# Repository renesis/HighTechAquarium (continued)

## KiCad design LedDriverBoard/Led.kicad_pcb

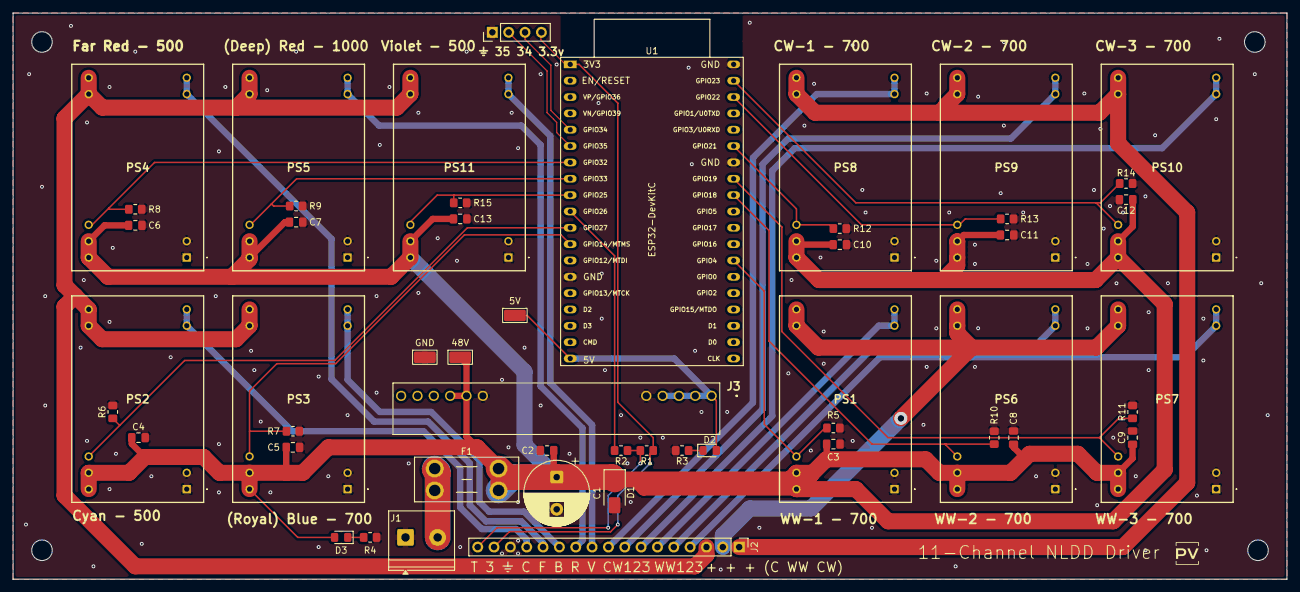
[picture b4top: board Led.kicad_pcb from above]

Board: 2 copper layers, 198.0 x 88.0 mm, 50 parts (0 on the bottom side), 34 nets.

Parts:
5V, 48V: TestPoint_Keystone_5015_Micro_Mini
C1: 220uF 63V; CP_Radial_D10.0mm_P5.00mm
C2: 0.1uF; C_0805_2012Metric_Pad1.18x1.45mm_HandSolder
C3, C4, C5, C6, C7, C8, C9, C10, C11, C12, C13: 2.2uF; C_0805_2012Metric_Pad1.18x1.45mm_HandSolder
D1: SMAJ48A; D_SMA
D2, D3: LED; LED_0805_2012Metric_Pad1.15x1.40mm_HandSolder
F1: 5A; Fuseholder_Blade_Mini_Keystone_3568
GND: TestPoint_Keystone_5015_Micro_Mini
J1: 48V IN; TerminalBlock_Phoenix_PT-1,5-2-5.0-H_1x02_P5.00mm_Horizontal
J2: Conn_01x17; PinHeader_1x17_P2.54mm_Vertical
J3: NID35-5; NID355
PS1, PS2, PS3, PS4, PS5, PS6, PS7, PS8, PS9, PS10, PS11: NLDD-700H; NLDD700H
R1: 4.7k; R_0805_2012Metric_Pad1.20x1.40mm_HandSolder
R2: 100R; R_0805_2012Metric_Pad1.20x1.40mm_HandSolder
R3: 1k; R_0805_2012Metric_Pad1.20x1.40mm_HandSolder
R4: 22k; R_0805_2012Metric_Pad1.20x1.40mm_HandSolder
R5, R6, R7, R8, R9, R10, R11, R12, R13, R14, R15: 10k; R_0805_2012Metric_Pad1.20x1.40mm_HandSolder
U1: ESP32-DevKitC

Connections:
+3V3: J2.16, R1.1, U1.1 (3V3)
+5V: 5V.1, D2.2 (A), J3.1 (+VOUT_1), J3.2 (+VOUT_2), J3.3 (+VOUT_3), J3.4 (+VOUT_4), U1.19 (5V)
+48V: 48V.1, C1.1, C2.1, C3.1, C4.1, C5.1, C6.1, C7.1, C8.1, C9.1, C10.1, C11.1, C12.1, C13.1, D1.1 (A1), D3.2 (A), F1.2, J3.7 (+VIN_1), J3.8 (+VIN_2), PS1.23 (+VIN_1), PS1.24 (+VIN_2), PS2.23 (+VIN_1), PS2.24 (+VIN_2), PS3.23 (+VIN_1), PS3.24 (+VIN_2), PS4.23 (+VIN_1), PS4.24 (+VIN_2), PS5.23 (+VIN_1), PS5.24 (+VIN_2), PS6.23 (+VIN_1), PS6.24 (+VIN_2), PS7.23 (+VIN_1), PS7.24 (+VIN_2), PS8.23 (+VIN_1), PS8.24 (+VIN_2), PS9.23 (+VIN_1), PS9.24 (+VIN_2), PS10.23 (+VIN_1), PS10.24 (+VIN_2), PS11.23 (+VIN_1), PS11.24 (+VIN_2)
GND: C1.2, C2.2, C3.2, C4.2, C5.2, C6.2, C7.2, C8.2, C9.2, C10.2, C11.2, C12.2, C13.2, D1.2 (A2), GND.1, J1.1, J2.15, J3.5 (COM_1), J3.6 (COM_2), PS1.1 (-VIN_1), PS1.2 (-VIN_2), PS2.1 (-VIN_1), PS2.2 (-VIN_2), PS3.1 (-VIN_1), PS3.2 (-VIN_2), PS4.1 (-VIN_1), PS4.2 (-VIN_2), PS5.1 (-VIN_1), PS5.2 (-VIN_2), PS6.1 (-VIN_1), PS6.2 (-VIN_2), PS7.1 (-VIN_1), PS7.2 (-VIN_2), PS8.1 (-VIN_1), PS8.2 (-VIN_2), PS9.1 (-VIN_1), PS9.2 (-VIN_2), PS10.1 (-VIN_1), PS10.2 (-VIN_2), PS11.1 (-VIN_1), PS11.2 (-VIN_2), R3.2, R4.2, R5.2, R6.2, R7.2, R8.2, R9.2, R10.2, R11.2, R12.2, R13.2, R14.2, R15.2, U1.14 (GND), U1.32 (GND), U1.38 (GND)
LEDCOLOR+: J2.3, PS2.13 (+VOUT_1), PS2.14 (+VOUT_2), PS3.13 (+VOUT_1), PS3.14 (+VOUT_2), PS4.13 (+VOUT_1), PS4.14 (+VOUT_2), PS5.13 (+VOUT_1), PS5.14 (+VOUT_2), PS11.13 (+VOUT_1), PS11.14 (+VOUT_2)
LEDCW+: J2.1, PS8.13 (+VOUT_1), PS8.14 (+VOUT_2), PS9.13 (+VOUT_1), PS9.14 (+VOUT_2), PS10.13 (+VOUT_1), PS10.14 (+VOUT_2)
LEDWW+: J2.2, PS1.13 (+VOUT_1), PS1.14 (+VOUT_2), PS6.13 (+VOUT_1), PS6.14 (+VOUT_2), PS7.13 (+VOUT_1), PS7.14 (+VOUT_2)
LED_CH1-: J2.6, PS1.11 (-VOUT_1), PS1.12 (-VOUT_2)
LED_CH2-: J2.14, PS2.11 (-VOUT_1), PS2.12 (-VOUT_2)
LED_CH3-: J2.12, PS3.11 (-VOUT_1), PS3.12 (-VOUT_2)
LED_CH4-: J2.13, PS4.11 (-VOUT_1), PS4.12 (-VOUT_2)
LED_CH5-: J2.11, PS5.11 (-VOUT_1), PS5.12 (-VOUT_2)
LED_CH6-: J2.5, PS6.11 (-VOUT_1), PS6.12 (-VOUT_2)
LED_CH7-: J2.4, PS7.11 (-VOUT_1), PS7.12 (-VOUT_2)
LED_CH8-: J2.9, PS8.11 (-VOUT_1), PS8.12 (-VOUT_2)
LED_CH9-: J2.8, PS9.11 (-VOUT_1), PS9.12 (-VOUT_2)
LED_CH10-: J2.7, PS10.11 (-VOUT_1), PS10.12 (-VOUT_2)
LED_CH11-: J2.10, PS11.11 (-VOUT_1), PS11.12 (-VOUT_2)
unnamed: D2.1 (K), R3.1
unnamed: D3.1 (K), R4.1
unnamed: F1.1, J1.2
unnamed: R2.2, U1.10 (DAC_2/ADC2_CH9/GPIO26)
PWM_CH1: PS1.22 (PWM_DIM), R5.1, U1.26 (ADC2_CH0/GPIO4)
PWM_CH2: PS2.22 (PWM_DIM), R6.1, U1.11 (ADC2_CH7/GPIO27)
PWM_CH3: PS3.22 (PWM_DIM), R7.1, U1.12 (MTMS/GPIO14/ADC2_CH6)
PWM_CH4: PS4.22 (PWM_DIM), R8.1, U1.7 (32K_XP/GPIO32/ADC1_CH4)
PWM_CH5: PS5.22 (PWM_DIM), R9.1, U1.8 (32K_XN/GPIO33/ADC1_CH5)
PWM_CH6: PS6.22 (PWM_DIM), R10.1, U1.30 (GPIO18)
PWM_CH7: PS7.22 (PWM_DIM), R11.1, U1.31 (GPIO19)
PWM_CH8: PS8.22 (PWM_DIM), R12.1, U1.33 (GPIO21)
PWM_CH9: PS9.22 (PWM_DIM), R13.1, U1.36 (GPIO22)
PWM_CH10: PS10.22 (PWM_DIM), R14.1, U1.37 (GPIO23)
PWM_CH11: PS11.22 (PWM_DIM), R15.1, U1.9 (DAC_1/ADC2_CH8/GPIO25)
TEMP_DATA: J2.17, R1.2, R2.1

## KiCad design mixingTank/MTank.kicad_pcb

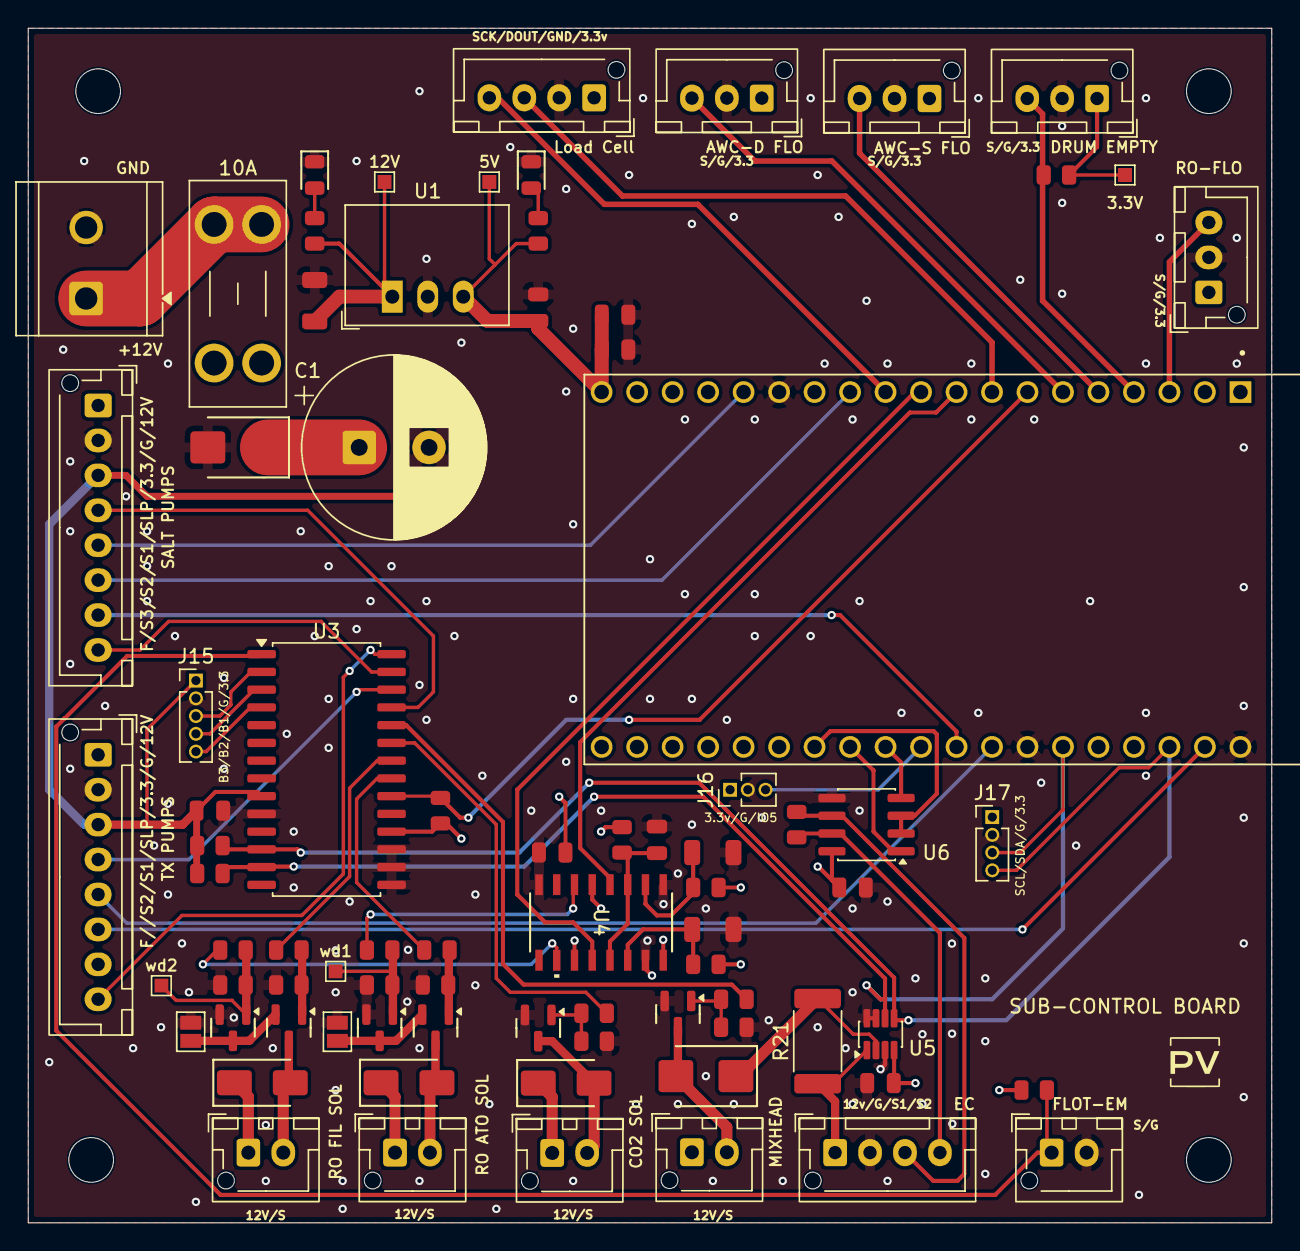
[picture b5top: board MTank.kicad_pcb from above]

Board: 4 copper layers, 89.0 x 85.5 mm, 80 parts (0 on the bottom side), 59 nets.

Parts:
3.3V, 5V, 12V: TestPoint; TestPoint_Pad_1.0x1.0mm
10A: 10A; Fuseholder_Blade_Mini_Keystone_3568
AWC-D FLO: AWC-FLO D; JST_XH_B3B-XH-AM_1x03_P2.50mm_Vertical
AWC-S FLO: AWC-FLO; JST_XH_B3B-XH-AM_1x03_P2.50mm_Vertical
C1: 1000uF; CP_Radial_D13.0mm_P5.00mm
C2: 22uF; C_0805
C3: 10uF; C_0805
C4, C7, C8: 10uF; C_1206
C5, C6, C10, C11, C12: 100nF; C_0805
C9: 1uF; C_0805
CO2 SOL: CO2 SOL; JST_XH_B2B-XH-AM_1x02_P2.50mm_Vertical
D1: SMBJ16A; D_SMB
D2, D3: Green; D_0805
D4, D5, D6: SS14; D_SMA
D8: SS24; D_SMB
DRUM EMPTY: DRUM; JST_XH_B3B-XH-AM_1x03_P2.50mm_Vertical
EC: EC Probe; JST_XH_B4B-XH-AM_1x04_P2.50mm_Vertical
FLOT-EM: EM; JST_XH_B2B-XH-AM_1x02_P2.50mm_Vertical
J1: 12V IN; TerminalBlock_CUI_TB007-508-02_1x02_P5.08mm_Horizontal
J15: Conn_01x05; PinHeader_1x05_P1.27mm_Vertical
J16: Screw_Terminal_01x03; PinHeader_1x03_P1.27mm_Vertical
J17: Conn_01x04; PinHeader_1x04_P1.27mm_Vertical
JP1, JP2: WD Bypass; SolderJumper-2_P1.3mm_Open_Pad1.0x1.5mm
Load Cell: LoadCell; JST_XH_B4B-XH-AM_1x04_P2.50mm_Vertical
MIXHEAD: CO2 SOL; JST_XH_B2B-XH-AM_1x02_P2.50mm_Vertical
Q1, Q2, Q3, Q4, Q5, Q6: AO3400A; Q_SOT-23
R1: 2.2kΩ; R_0805
R2: 1kΩ; R_0805
R3, R4: 4.7kΩ; R_0805
R5, R7, R10, R13, R14, R16, R18, R20, R23, R24: 10kΩ; R_0805
R6, R11, R12, R15, R17, R19: 100Ω; R_0805
R8, R9: 470kΩ; R_0805
R21: PE2512FKE070R1L; R_2512_6332Metric_Pad1.40x3.35mm_HandSolder
R22: 120Ω; R_0805
RO ATO SOL: RO SOL; JST_XH_B2B-XH-AM_1x02_P2.50mm_Vertical
RO FIL SOL: RO SOL ATO; JST_XH_B2B-XH-AM_1x02_P2.50mm_Vertical
RO-FLO: RO FLO; JST_XH_B3B-XH-AM_1x03_P2.50mm_Vertical
SALT PUMPS: SALT; JST_XH_B8B-XH-AM_1x08_P2.50mm_Vertical
TX PUMPS: AWC; JST_XH_B8B-XH-AM_1x08_P2.50mm_Vertical
U1: R-78C5.0-1.0; Converter_DCDC_RECOM_R-78E-0.5_THT
U2: ESP32-DEVKITC-32UE; ESPRESSIF_ESP32-DEVKITC-32UE
U3: MCP23017_SO; SOIC-28W_7.5x17.9mm_P1.27mm
U4: MC14538BDR2G; SOIC-16_ONS
U5: INA219BxDCN; SOT-23-8
U6: SN65HVD78DR; SOIC-8_3.9x4.9mm_P1.27mm
wd1, wd2: TestPoint; TestPoint_Pad_1.0x1.0mm

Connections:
+3.3V: 3.3V.1 (1_1), AWC-D FLO.1, AWC-S FLO.1, C6.1, C10.1, C11.1, C12.1, DRUM EMPTY.1, J15.1, J16.1, J17.1, Load Cell.1, R3.1, R4.1, R5.1, R8.1, R9.1, R10.1, R23.1, R24.1, RO-FLO.1, SALT PUMPS.3, TX PUMPS.3, U2.1 (3V3), U3.9 (VDD), U3.18 (~RESET), U4.5 (*BA), U4.11 (*BB), U4.16 (VDD), U5.4 (VS), U6.8 (VCC)
+5V: 5V.1 (1_1), C2.1, C3.1, C5.1, R2.1, U1.3 (OUT), U2.19 (5V)
+12V: 10A.1, J1.1
+12VF: 10A.2, 12V.1 (1_1), C1.1, C4.1, CO2 SOL.1, D1.1 (K), D4.1 (K), D5.1 (K), D6.1 (K), EC.1, MIXHEAD.1, R1.1, R21.1, RO ATO SOL.1, RO FIL SOL.1, SALT PUMPS.1, TX PUMPS.1, U1.1 (IN), U5.1 (IN+)
AWC-FAULT: TX PUMPS.8, U3.28 (GPA7)
AWC-SLEEP: TX PUMPS.4, U3.26 (GPA5)
COSOL-: CO2 SOL.2, D6.2 (A), Q5.3 (D)
FLO-AWC-D: AWC-D FLO.3, U2.6 (35)
FLO-AWC-S: AWC-S FLO.3, U2.5 (34)
FLO-RO: RO-FLO.3, U2.3 (VP)
FLOAT-EM: FLOT-EM.1, R24.2, U3.1 (GPB0)
GND: AWC-D FLO.2, AWC-S FLO.2, C1.2, C2.2, C3.2, C4.2, C5.2, C6.2, C7.2, C8.2, C9.2, C10.2, C11.2, C12.2, D1.2 (A), D2.1, D3.1, DRUM EMPTY.2, EC.2, FLOT-EM.2, J1.2, J15.2, J16.2, J17.2, JP1.2 (B), JP2.2 (B), Load Cell.2, Q2.2 (S), Q4.2 (S), Q5.2 (S), Q6.2 (S), R7.2, R13.2, R14.2, R16.2, R18.2, R20.2, RO-FLO.2, SALT PUMPS.2, TX PUMPS.2, U1.2 (GND), U2.14 (GND), U2.20 (GND__1), U2.26 (GND__2), U3.10 (VSS), U3.15 (A0), U3.16 (A1), U3.17 (A2), U4.1 (VSS), U4.8 (VSS), U4.15 (VSS), U5.3 (GND), U5.7 (A0), U5.8 (A1), U6.5 (GND)
GPB1: J15.3, U3.2 (GPB1)
GPB2: J15.4, U3.3 (GPB2)
GPB3: J15.5, U3.4 (GPB3)
GPIO5: J16.3, U2.29 (5)
HX711-DOUT: Load Cell.3, U2.8 (33)
HX711-SCK: Load Cell.4, U2.11 (27)
INTA: R5.2, U2.7 (32), U3.20 (INTA)
MIXHEAD: R19.1, U3.24 (GPA3)
MIXHEAD-: D8.2 (A), MIXHEAD.2, Q6.3 (D)
unnamed: D2.2, R1.2
unnamed: D3.2, R2.2
unnamed: D8.1 (K), R21.2, U5.2 (IN-)
unnamed: EC.3, R22.2, U6.6 (A)
unnamed: EC.4, R22.1, U6.7 (B)
unnamed: JP1.1 (A), Q1.2 (S), Q2.3 (D)
unnamed: JP2.1 (A), Q3.2 (S), Q4.3 (D)
unnamed: Q1.1 (G), R6.2, R7.1
unnamed: Q3.1 (G), R15.2, R16.1
unnamed: Q5.1 (G), R17.2, R18.1
unnamed: Q6.1 (G), R19.2, R20.1
unnamed: C7.1, R8.2, U4.2 (CX/RXA)
unnamed: C8.1, R9.2, U4.14 (CX/RXB)
unnamed: R12.2, U4.6 (QA)
unnamed: R11.2, U4.10 (QB)
ROSOL2-: D5.2 (A), Q3.3 (D), RO FIL SOL.2
ROSOL-: D4.2 (A), Q1.3 (D), RO ATO SOL.2
RS485DE/RE: U2.32 (4), U6.2 (~RE), U6.3 (DE)
RS485RX: U2.31 (16), U6.1 (R)
RS485TX: U2.30 (17), U6.4 (D)
RST: C9.1, R10.2, U4.3 (*RESETA), U4.13 (*RESETB)
SALT-FAULT: SALT PUMPS.8, U3.27 (GPA6)
SALT-SLEEP: SALT PUMPS.4, U3.25 (GPA4)
SCL: J17.4, R4.2, U2.22, U3.12 (SCK), U5.5 (SCL)
SDA: J17.3, R3.2, U2.25 (21), U3.13 (SDA), U5.6 (SDA)
SOL-CO2: R17.1, U3.23 (GPA2)
SOL-RO: R6.1, U3.21 (GPA0)
SOL-RO-ATO: R15.1, U3.22 (GPA1)
STEP1: SALT PUMPS.5, U2.15 (13)
STEP2: SALT PUMPS.6, U2.12 (14)
STEP3: SALT PUMPS.7, U2.28 (18)
TSTEP1: TX PUMPS.5, U2.27 (19)
TSTEP2: TX PUMPS.6, U2.21 (23)
WD1: U2.9 (25), U4.4 (AA)
WD1GATE: Q2.1 (G), R12.1, R14.1, wd1.1 (1_1)
WD2: U2.10 (26), U4.12 (AB)
WD2GATE: Q4.1 (G), R11.1, R13.1, wd2.1 (1_1)
XKC-DRUM: DRUM EMPTY.3, R23.2, U2.4 (VN)
